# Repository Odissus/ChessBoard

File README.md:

# About

An interactive chess board hardware design based on Arduino Nano ESP32 and KiCad.

| Top | Bottom |
| :---: | :---: |
|  |  |

> [!TIP]
> If you're just interested in manufacturing your own board, see the quick-start section below

It includes:

* Main schematic and PCB project files
* Local symbol, footprint, and 3D model libraries under `lib/`
* Manufacturing export artifacts under `jlcpcbProduction/`
* Utility scripts under `scripts/` for project-related automation

The goal is to keep everything needed to inspect, edit, and manufacture the board inside this repository.

This PCB is based on [Concept Bytes design](https://concept-bytes.com/products/openchess-pcb), along with their [GitHub repository](https://github.com/Concept-Bytes/Open-Chess). The design is new, although heavily insipired by their work and their guides should work in getting you set up on the embedded development side.

This design is optimised for [JLCPCB](https://jlcpcb.com/) production.

# Quick start

1. Head over to releases, and grab the `JLCPCB_Gerber.zip`, `JLCPCB_Bill_of_materials.csv` and `JLCPCB_Positions.csv` files from the latest release.
1. Heaver over to [JLCPCB](https://jlcpcb.com/) to get and instant PCB quote.
1. Upload the `JLCPCB_Gerber.zip`, let JLC process it.
1. Select your desired `PCB colour` (in PCB Specifications) - they're all free
1. Under High-spec Options, select `Mark on PCB` to `2D barcode Only`.
    1. For `Prefix`, choose a sensible name like `ChessBoard`
    1. For `2D Barcode Size` you must select `10*10mm`
    1. For `2D Barcode Position` select `Specify Position`
1. Select PCB Asembly - there is a choice here
    1. Default - economic. You'll have to source the `74HC595N` shift register yourself from a supplier like Mouser, DigiKey, Farnel or Amazon. Ensure you're buing a DIP-16. This should be relatively easy to solder and will reduce the costs by around 40%.
        1. For `PCBA Type`, select `Economic`
        1. For `Assembly Side`, select `Top Side`
        1. Unless you need 5 assembled boards, reduce `PCBA Qty` to `2`
        1. For `Tooling holes` select `Added by Customer`
    1. Standard. JLC will put the shift register in for you. I have not included edge rails or fiducials in the design.
        1. For `PCBA Type`, select `Standard`
        1. For `Assembly Side`, select `Both Sides`
        1. Unless you need 5 assembled boards, reduce `PCBA Qty` to `2`
        1. For `Edge Rails/Fiducials` select `Added by JLCPCB`. Their engineer will modify the design slightly to include the extra rails.
        1. In the `PCB Remark` section above, add in a note that you'd like to have V-cuts to create snappable edge rails.
1. Review your PCB, and click next
1. Upload `JLCPCB_Bill_of_materials.csv` as your BOM file and `JLCPCB_Positions.csv` as your CPL file. Let JLC process the files.
1. You should get the following different parts (assuming you're making 2 boards):
    - (2 * 64 = ) 128 LEDs 
    - (2 * 8 = ) 16 Resistors
    - (2 * 64 = ) 128 Hall effect sensors 
    - (2 * 1 = ) 2 Shift registers (this will only appear if you pick assembly on both sides)
1. Verify component placement i.e. does any part look out of place. If all is well, select next to get your final manufacture quote.
1. Profit?

## Setup

1. Install KiCad (recent stable version recommended).
2. Clone this repository.
3. Open `ChessBoard.kicad_pro` in KiCad.
4. Verify the project libraries resolve correctly (symbols, footprints, and 3D models under `lib/`).

Optional (for helper scripts):

1. Install Python 3.10+.
2. Create and activate a virtual environment.
3. Install script dependencies:

```bash
pip install -r scripts/requirements.txt
```

## Usage

Typical workflow:

1. Open the project in KiCad.
2. Edit schematics in `ChessBoard.kicad_sch` (and related sheets).
3. Update and route the PCB in `ChessBoard.kicad_pcb`.
4. Run DRC/ERC checks before export.
5. Generate manufacturing outputs and keep `jlcpcbProduction/` in sync when changes affect fabrication.

Optional helper scripts can be run from the repository root, for example:

```bash
python scripts/fix3D.py
python scripts/fixColours.py
python scripts/qr_detector.py
```

Review any generated or modified files before committing changes.

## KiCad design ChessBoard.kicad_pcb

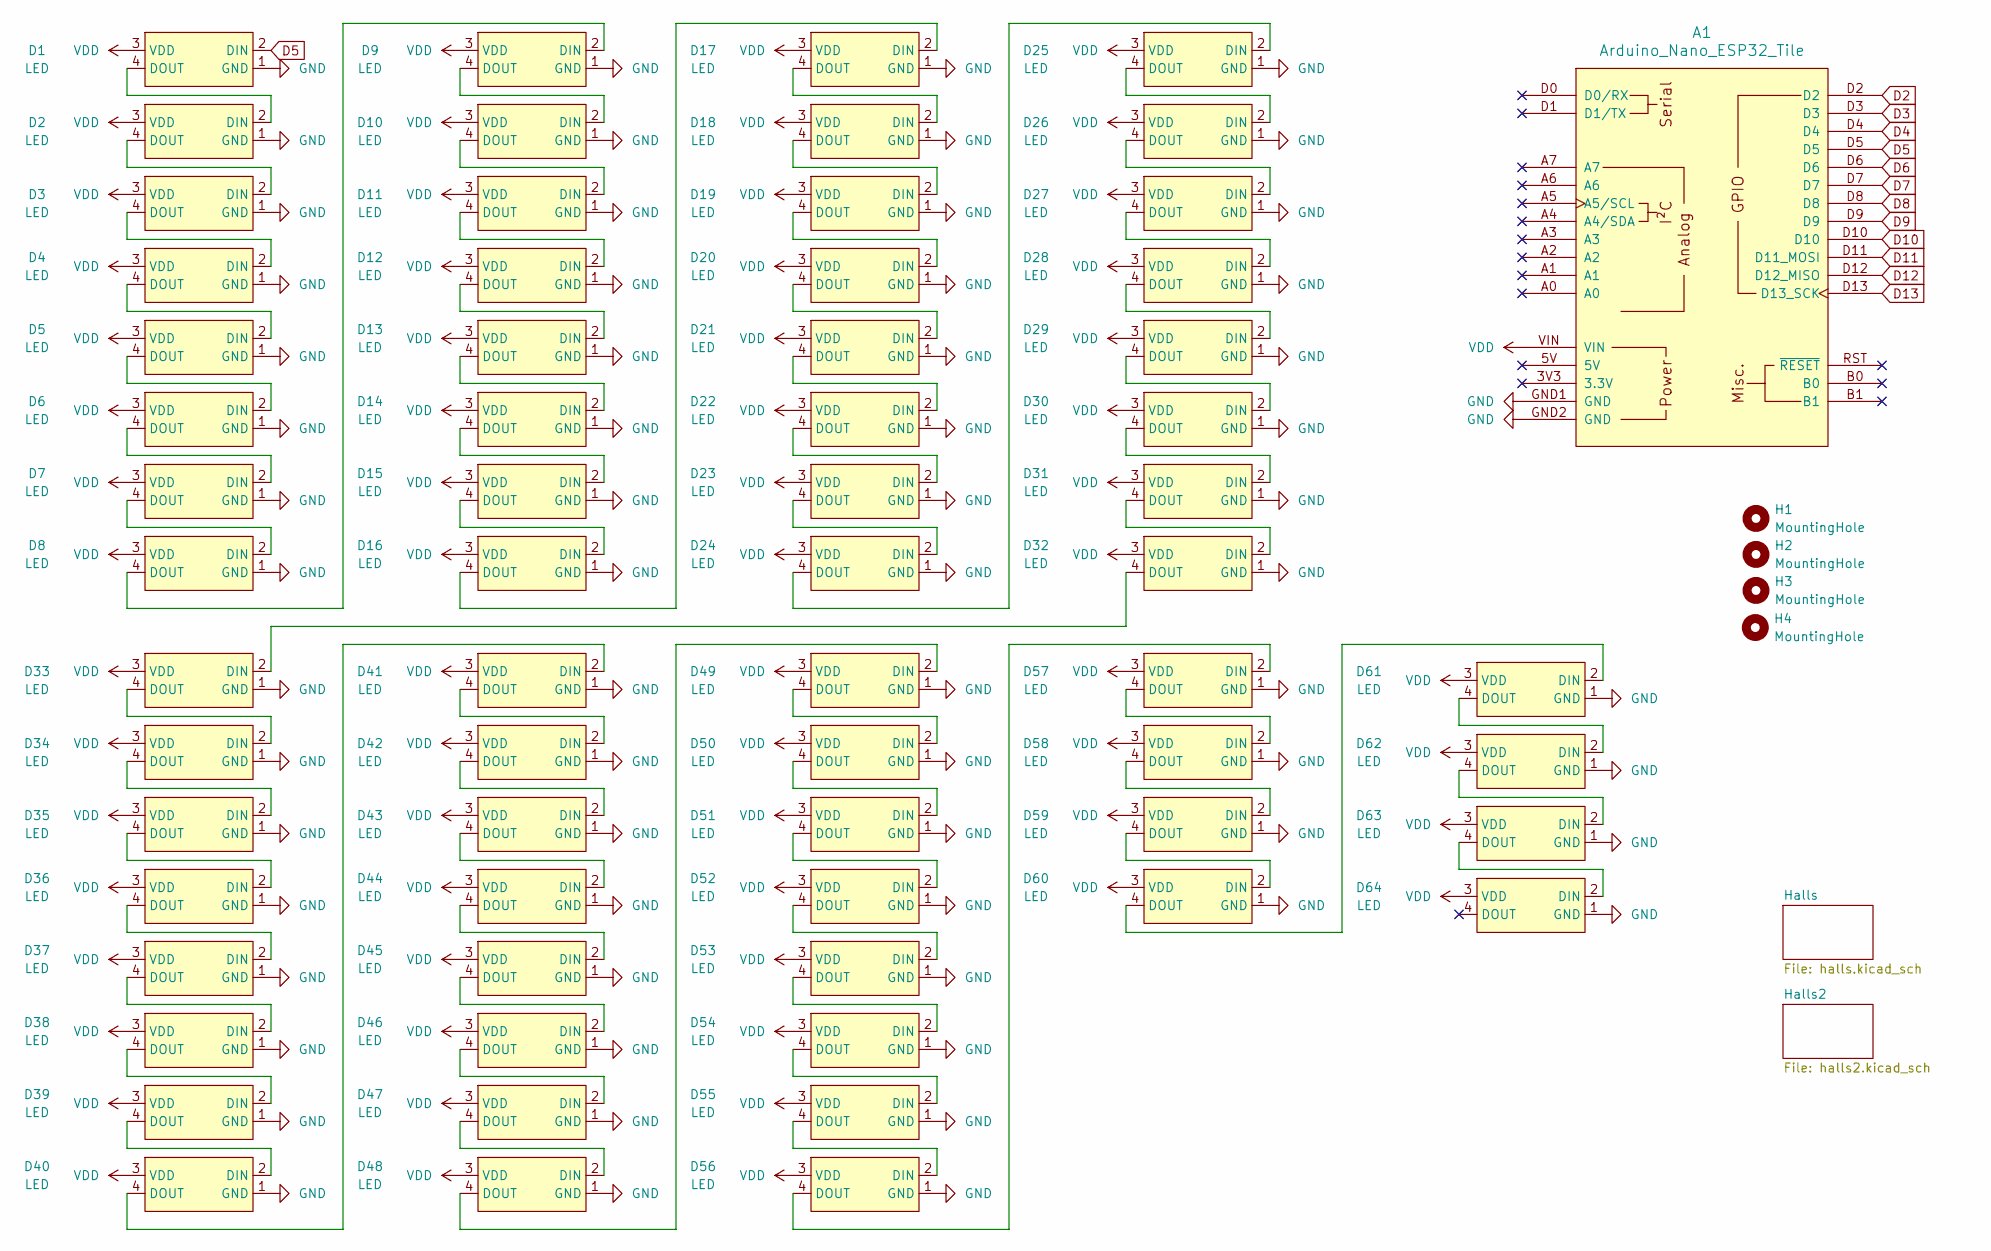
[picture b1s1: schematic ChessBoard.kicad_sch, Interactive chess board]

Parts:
A1: Arduino_Nano_ESP32_Tile
D1, D2, D3, D4, D5, D6, D7, D8, D9, D10, D11, D12, D13, D14, D15, D16, D17, D18, D19, D20, D21, D22, D23, D24, D25, D26, D27, D28, D29, D30, D31, D32, D33, D34, D35, D36, D37, D38, D39, D40, D41, D42, D43, D44, D45, D46, D47, D48, D49, D50, D51, D52, D53, D54, D55, D56, D57, D58, D59, D60, D61, D62, D63, D64: LED; LED-SMD_4P-L5.0-W5.0-TL-2; MPN SKC6812RGBW-BW-B; LCSC Part C5380878
H1, H2, H3, H4: MountingHole; MountingHole_2.1mm

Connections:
D2: A1.D2; also elsewhere on the board
D3: A1.D3; also elsewhere on the board
D4: A1.D4; also elsewhere on the board
D5: A1.D5, D1.2 (DIN)
D6: A1.D6; also elsewhere on the board
D7: A1.D7; also elsewhere on the board
D8: A1.D8; also elsewhere on the board
D9: A1.D9; also elsewhere on the board
D10: A1.D10; also elsewhere on the board
D11: A1.D11 (D11_MOSI); also elsewhere on the board
D12: A1.D12 (D12_MISO); also elsewhere on the board
D13: A1.D13 (D13_SCK); also elsewhere on the board
GND: A1.GND1 (GND), A1.GND2 (GND), D1.1 (GND), D2.1 (GND), D3.1 (GND), D4.1 (GND), D5.1 (GND), D6.1 (GND), D7.1 (GND), D8.1 (GND), D9.1 (GND), D10.1 (GND), D11.1 (GND), D12.1 (GND), D13.1 (GND), D14.1 (GND), D15.1 (GND), D16.1 (GND), D17.1 (GND), D18.1 (GND), D19.1 (GND), D20.1 (GND), D21.1 (GND), D22.1 (GND), D23.1 (GND), D24.1 (GND), D25.1 (GND), D26.1 (GND), D27.1 (GND), D28.1 (GND), D29.1 (GND), D30.1 (GND), D31.1 (GND), D32.1 (GND), D33.1 (GND), D34.1 (GND), D35.1 (GND), D36.1 (GND), D37.1 (GND), D38.1 (GND), D39.1 (GND), D40.1 (GND), D41.1 (GND), D42.1 (GND), D43.1 (GND), D44.1 (GND), D45.1 (GND), D46.1 (GND), D47.1 (GND), D48.1 (GND), D49.1 (GND), D50.1 (GND), D51.1 (GND), D52.1 (GND), D53.1 (GND), D54.1 (GND), D55.1 (GND), D56.1 (GND), D57.1 (GND), D58.1 (GND), D59.1 (GND), D60.1 (GND), D61.1 (GND), D62.1 (GND), D63.1 (GND), D64.1 (GND); also elsewhere on the board
unnamed: D1.4 (DOUT), D2.2 (DIN)
unnamed: D2.4 (DOUT), D3.2 (DIN)
unnamed: D3.4 (DOUT), D4.2 (DIN)
unnamed: D4.4 (DOUT), D5.2 (DIN)
unnamed: D5.4 (DOUT), D6.2 (DIN)
unnamed: D6.4 (DOUT), D7.2 (DIN)
unnamed: D7.4 (DOUT), D8.2 (DIN)
unnamed: D8.4 (DOUT), D9.2 (DIN)
unnamed: D9.4 (DOUT), D10.2 (DIN)
unnamed: D10.4 (DOUT), D11.2 (DIN)
unnamed: D11.4 (DOUT), D12.2 (DIN)
unnamed: D12.4 (DOUT), D13.2 (DIN)
unnamed: D13.4 (DOUT), D14.2 (DIN)
unnamed: D14.4 (DOUT), D15.2 (DIN)
unnamed: D15.4 (DOUT), D16.2 (DIN)
unnamed: D16.4 (DOUT), D17.2 (DIN)
unnamed: D17.4 (DOUT), D18.2 (DIN)
unnamed: D18.4 (DOUT), D19.2 (DIN)
unnamed: D19.4 (DOUT), D20.2 (DIN)
unnamed: D20.4 (DOUT), D21.2 (DIN)
unnamed: D21.4 (DOUT), D22.2 (DIN)
unnamed: D22.4 (DOUT), D23.2 (DIN)
unnamed: D23.4 (DOUT), D24.2 (DIN)
unnamed: D24.4 (DOUT), D25.2 (DIN)
unnamed: D25.4 (DOUT), D26.2 (DIN)
unnamed: D26.4 (DOUT), D27.2 (DIN)
unnamed: D27.4 (DOUT), D28.2 (DIN)
unnamed: D28.4 (DOUT), D29.2 (DIN)
unnamed: D29.4 (DOUT), D30.2 (DIN)
unnamed: D30.4 (DOUT), D31.2 (DIN)
unnamed: D31.4 (DOUT), D32.2 (DIN)
unnamed: D32.4 (DOUT), D33.2 (DIN)
unnamed: D33.4 (DOUT), D34.2 (DIN)
unnamed: D34.4 (DOUT), D35.2 (DIN)
unnamed: D35.4 (DOUT), D36.2 (DIN)
unnamed: D36.4 (DOUT), D37.2 (DIN)
unnamed: D37.4 (DOUT), D38.2 (DIN)
unnamed: D38.4 (DOUT), D39.2 (DIN)
unnamed: D39.4 (DOUT), D40.2 (DIN)
unnamed: D40.4 (DOUT), D41.2 (DIN)
unnamed: D41.4 (DOUT), D42.2 (DIN)
unnamed: D42.4 (DOUT), D43.2 (DIN)
unnamed: D43.4 (DOUT), D44.2 (DIN)
unnamed: D44.4 (DOUT), D45.2 (DIN)
unnamed: D45.4 (DOUT), D46.2 (DIN)
unnamed: D46.4 (DOUT), D47.2 (DIN)
unnamed: D47.4 (DOUT), D48.2 (DIN)
unnamed: D48.4 (DOUT), D49.2 (DIN)
unnamed: D49.4 (DOUT), D50.2 (DIN)
unnamed: D50.4 (DOUT), D51.2 (DIN)
unnamed: D51.4 (DOUT), D52.2 (DIN)
unnamed: D52.4 (DOUT), D53.2 (DIN)
unnamed: D53.4 (DOUT), D54.2 (DIN)
unnamed: D54.4 (DOUT), D55.2 (DIN)
unnamed: D55.4 (DOUT), D56.2 (DIN)
unnamed: D56.4 (DOUT), D57.2 (DIN)
unnamed: D57.4 (DOUT), D58.2 (DIN)
unnamed: D58.4 (DOUT), D59.2 (DIN)
unnamed: D59.4 (DOUT), D60.2 (DIN)
unnamed: D60.4 (DOUT), D61.2 (DIN)
unnamed: D61.4 (DOUT), D62.2 (DIN)
unnamed: D62.4 (DOUT), D63.2 (DIN)
unnamed: D63.4 (DOUT), D64.2 (DIN)
VDD: A1.VIN, D1.3 (VDD), D2.3 (VDD), D3.3 (VDD), D4.3 (VDD), D5.3 (VDD), D6.3 (VDD), D7.3 (VDD), D8.3 (VDD), D9.3 (VDD), D10.3 (VDD), D11.3 (VDD), D12.3 (VDD), D13.3 (VDD), D14.3 (VDD), D15.3 (VDD), D16.3 (VDD), D17.3 (VDD), D18.3 (VDD), D19.3 (VDD), D20.3 (VDD), D21.3 (VDD), D22.3 (VDD), D23.3 (VDD), D24.3 (VDD), D25.3 (VDD), D26.3 (VDD), D27.3 (VDD), D28.3 (VDD), D29.3 (VDD), D30.3 (VDD), D31.3 (VDD), D32.3 (VDD), D33.3 (VDD), D34.3 (VDD), D35.3 (VDD), D36.3 (VDD), D37.3 (VDD), D38.3 (VDD), D39.3 (VDD), D40.3 (VDD), D41.3 (VDD), D42.3 (VDD), D43.3 (VDD), D44.3 (VDD), D45.3 (VDD), D46.3 (VDD), D47.3 (VDD), D48.3 (VDD), D49.3 (VDD), D50.3 (VDD), D51.3 (VDD), D52.3 (VDD), D53.3 (VDD), D54.3 (VDD), D55.3 (VDD), D56.3 (VDD), D57.3 (VDD), D58.3 (VDD), D59.3 (VDD), D60.3 (VDD), D61.3 (VDD), D62.3 (VDD), D63.3 (VDD), D64.3 (VDD); also elsewhere on the board

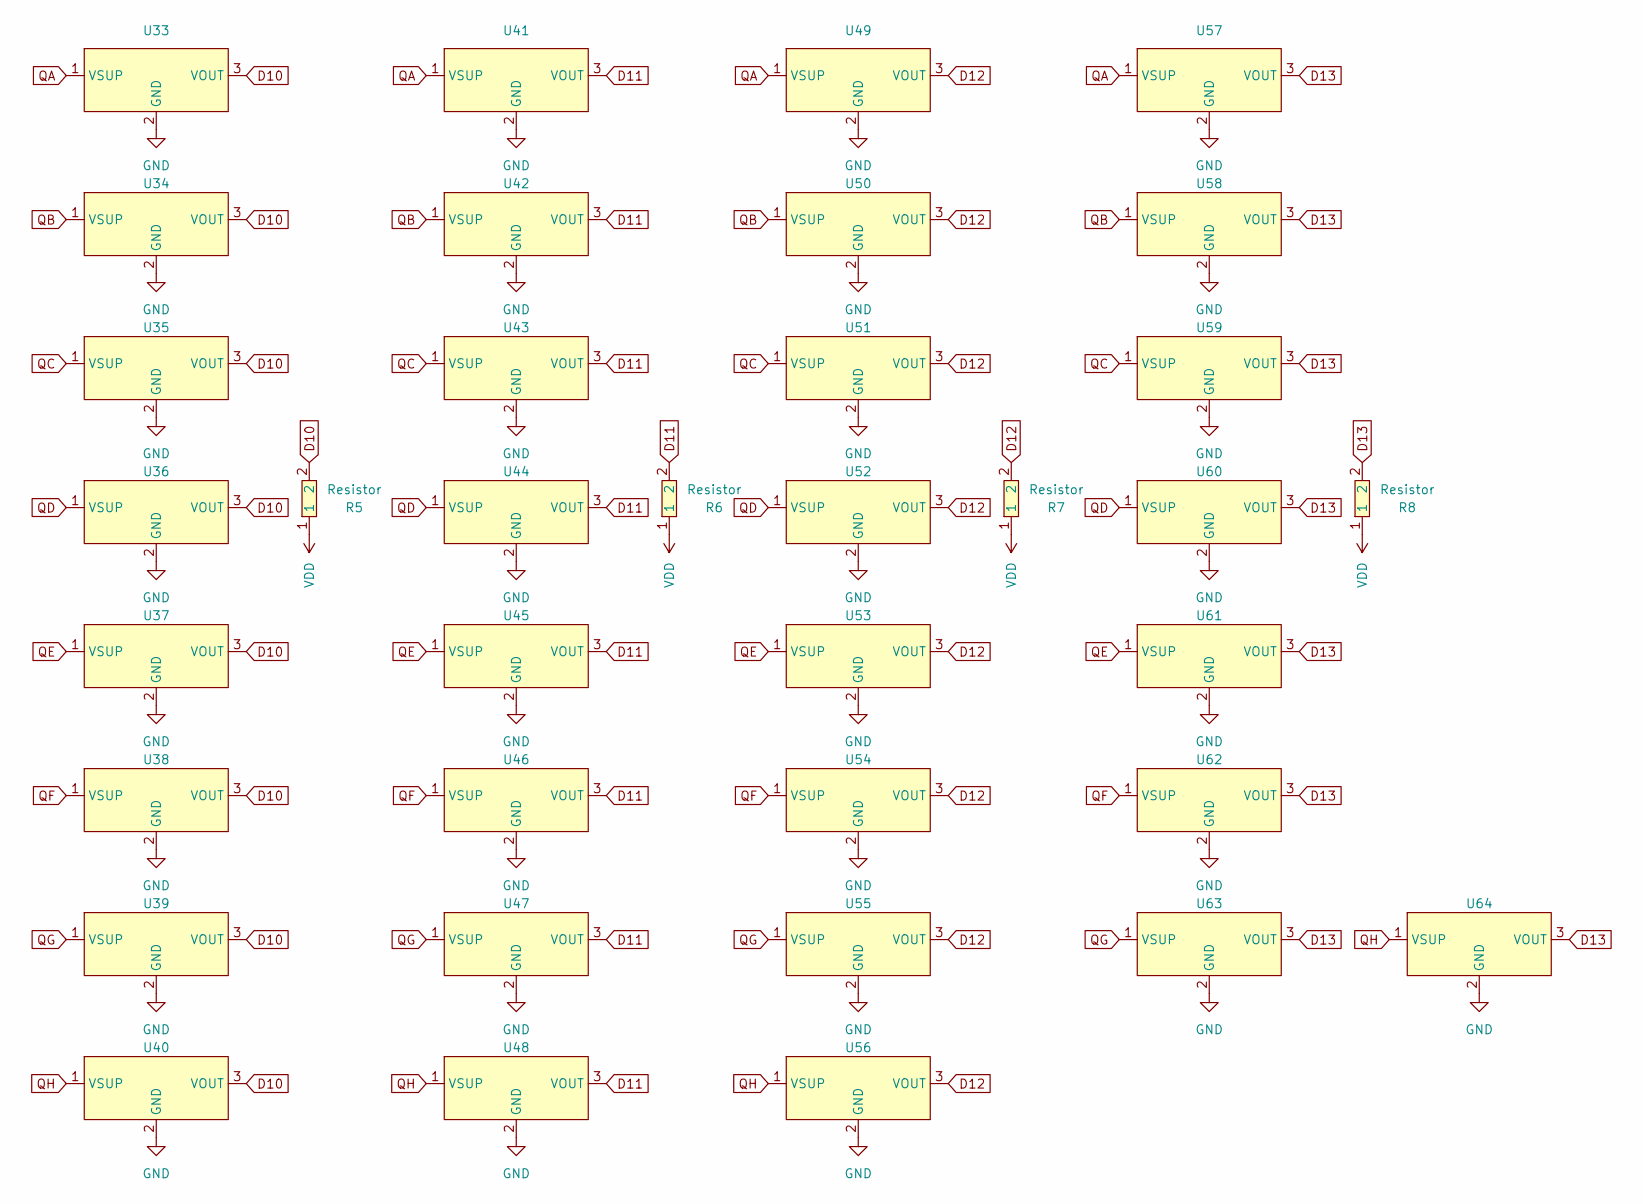
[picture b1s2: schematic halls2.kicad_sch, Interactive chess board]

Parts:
R5, R6, R7, R8: Resistor; R0805; MPN 0805W8F1002T5E; LCSC Part C17414
U33, U34, U35, U36, U37, U38, U39, U40, U41, U42, U43, U44, U45, U46, U47, U48, U49, U50, U51, U52, U53, U54, U55, U56, U57, U58, U59, U60, U61, U62, U63, U64: Hall; SOT-23-3_L2.9-W1.6-P1.90-LS2.8-BR-CW; MPN A3144E-JSM; LCSC Part C18221462

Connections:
D10: R5.2, U33.3 (VOUT), U34.3 (VOUT), U35.3 (VOUT), U36.3 (VOUT), U37.3 (VOUT), U38.3 (VOUT), U39.3 (VOUT), U40.3 (VOUT); also elsewhere on the board
D11: R6.2, U41.3 (VOUT), U42.3 (VOUT), U43.3 (VOUT), U44.3 (VOUT), U45.3 (VOUT), U46.3 (VOUT), U47.3 (VOUT), U48.3 (VOUT); also elsewhere on the board
D12: R7.2, U49.3 (VOUT), U50.3 (VOUT), U51.3 (VOUT), U52.3 (VOUT), U53.3 (VOUT), U54.3 (VOUT), U55.3 (VOUT), U56.3 (VOUT); also elsewhere on the board
D13: R8.2, U57.3 (VOUT), U58.3 (VOUT), U59.3 (VOUT), U60.3 (VOUT), U61.3 (VOUT), U62.3 (VOUT), U63.3 (VOUT), U64.3 (VOUT); also elsewhere on the board
GND: U33.2 (GND), U34.2 (GND), U35.2 (GND), U36.2 (GND), U37.2 (GND), U38.2 (GND), U39.2 (GND), U40.2 (GND), U41.2 (GND), U42.2 (GND), U43.2 (GND), U44.2 (GND), U45.2 (GND), U46.2 (GND), U47.2 (GND), U48.2 (GND), U49.2 (GND), U50.2 (GND), U51.2 (GND), U52.2 (GND), U53.2 (GND), U54.2 (GND), U55.2 (GND), U56.2 (GND), U57.2 (GND), U58.2 (GND), U59.2 (GND), U60.2 (GND), U61.2 (GND), U62.2 (GND), U63.2 (GND), U64.2 (GND); also elsewhere on the board
QA: U33.1 (VSUP), U41.1 (VSUP), U49.1 (VSUP), U57.1 (VSUP); also elsewhere on the board
QB: U34.1 (VSUP), U42.1 (VSUP), U50.1 (VSUP), U58.1 (VSUP); also elsewhere on the board
QC: U35.1 (VSUP), U43.1 (VSUP), U51.1 (VSUP), U59.1 (VSUP); also elsewhere on the board
QD: U36.1 (VSUP), U44.1 (VSUP), U52.1 (VSUP), U60.1 (VSUP); also elsewhere on the board
QE: U37.1 (VSUP), U45.1 (VSUP), U53.1 (VSUP), U61.1 (VSUP); also elsewhere on the board
QF: U38.1 (VSUP), U46.1 (VSUP), U54.1 (VSUP), U62.1 (VSUP); also elsewhere on the board
QG: U39.1 (VSUP), U47.1 (VSUP), U55.1 (VSUP), U63.1 (VSUP); also elsewhere on the board
QH: U40.1 (VSUP), U48.1 (VSUP), U56.1 (VSUP), U64.1 (VSUP); also elsewhere on the board
VDD: R5.1, R6.1, R7.1, R8.1; also elsewhere on the board

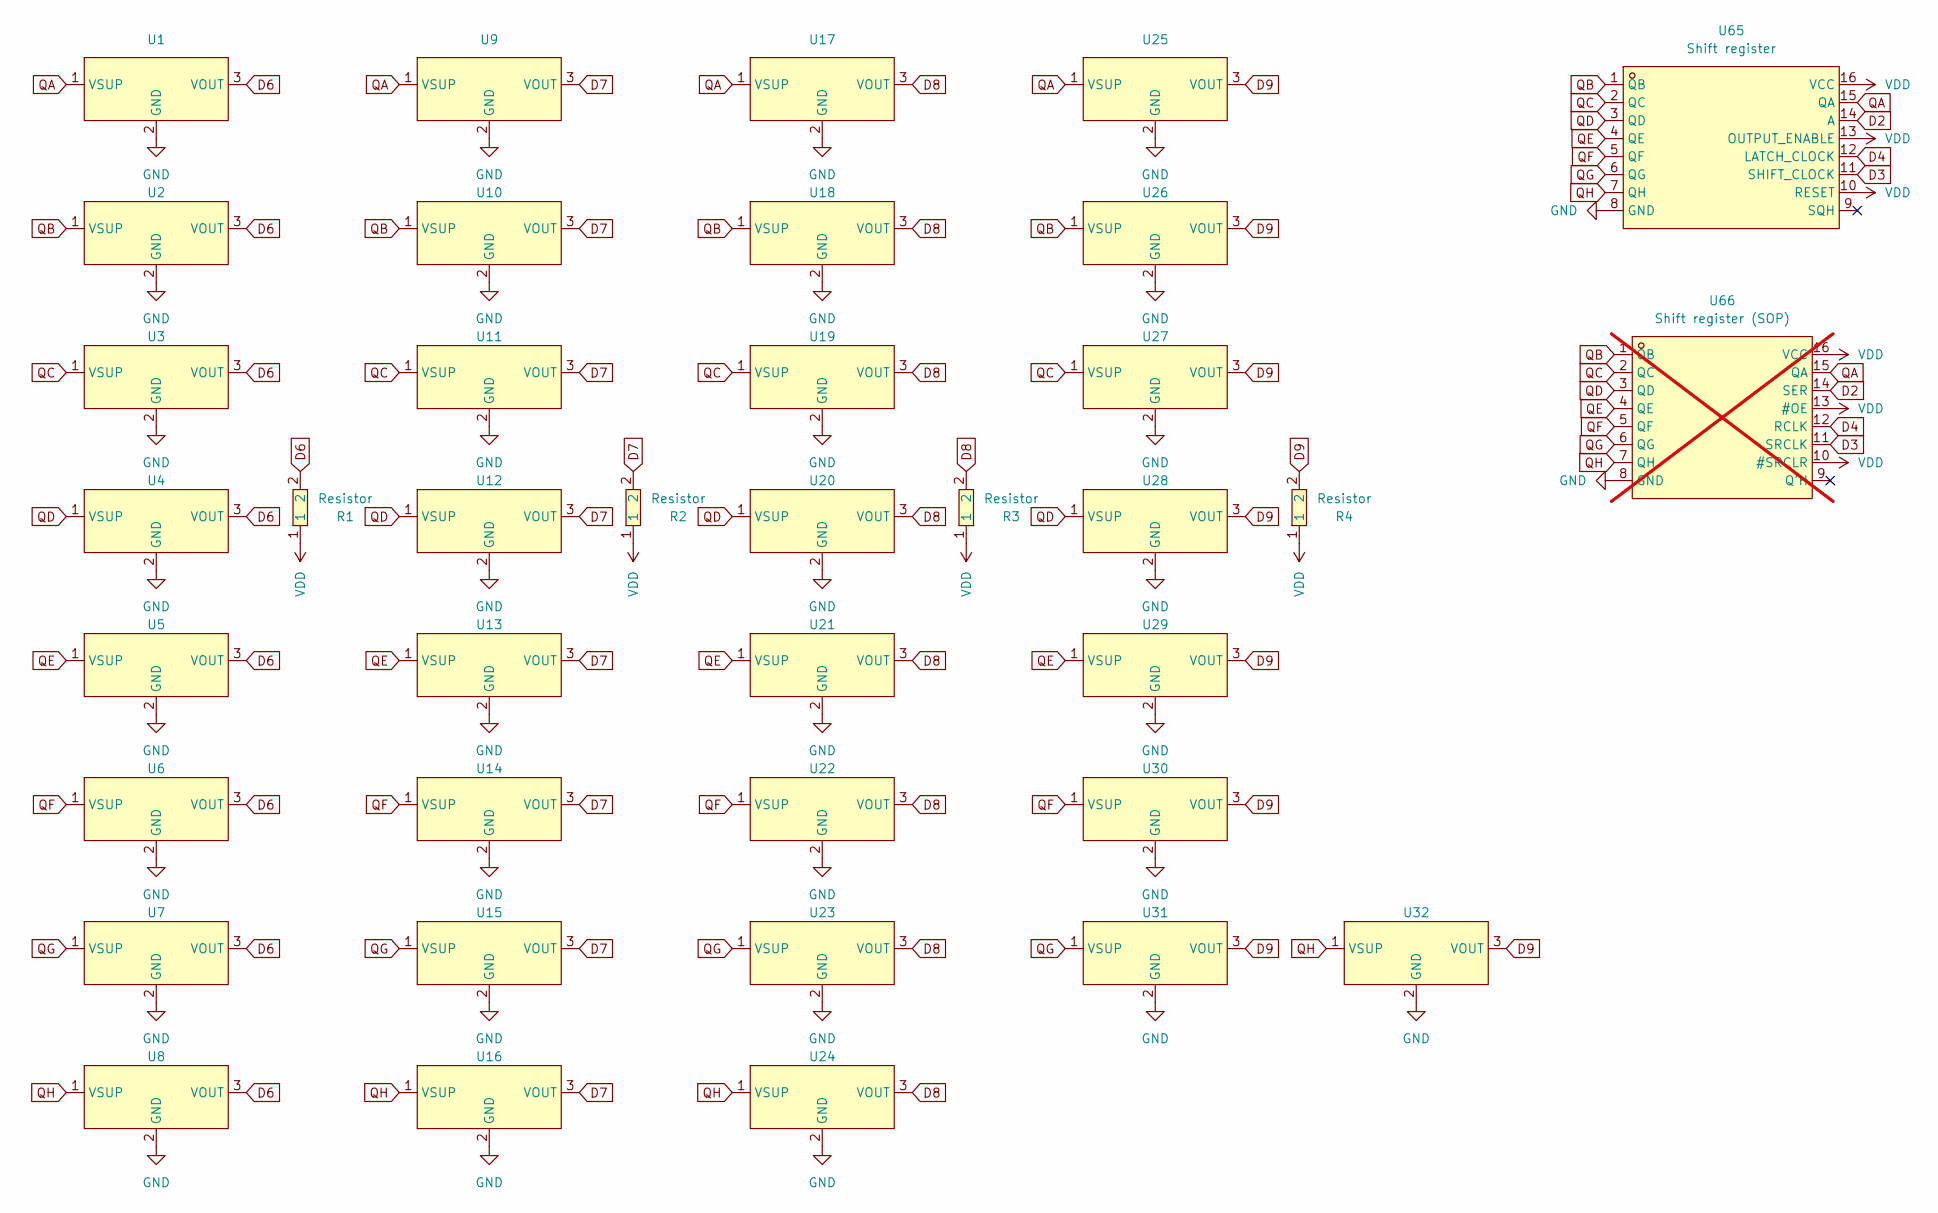
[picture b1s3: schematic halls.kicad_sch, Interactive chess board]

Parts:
R1, R2, R3, R4: Resistor; R0805; MPN 0805W8F1002T5E; LCSC Part C17414
U1, U2, U3, U4, U5, U6, U7, U8, U9, U10, U11, U12, U13, U14, U15, U16, U17, U18, U19, U20, U21, U22, U23, U24, U25, U26, U27, U28, U29, U30, U31, U32: Hall; SOT-23-3_L2.9-W1.6-P1.90-LS2.8-BR-CW; MPN A3144E-JSM; LCSC Part C18221462
U65: Shift register; DIP-16_L20.0-W6.4-P2.54-LS7.6-BL; MPN 74HC595N; LCSC Part C507175
U66: Shift register (SOP); SOP-16_L10.3-W5.4-P1.27-LS7.8-BL; MPN SN74HC595NSR; LCSC Part C191873; not fitted

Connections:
D2: U65.14 (A), U66.14 (SER); also elsewhere on the board
D3: U65.11 (SHIFT_CLOCK), U66.11 (SRCLK); also elsewhere on the board
D4: U65.12 (LATCH_CLOCK), U66.12 (RCLK); also elsewhere on the board
D6: R1.2, U1.3 (VOUT), U2.3 (VOUT), U3.3 (VOUT), U4.3 (VOUT), U5.3 (VOUT), U6.3 (VOUT), U7.3 (VOUT), U8.3 (VOUT); also elsewhere on the board
D7: R2.2, U9.3 (VOUT), U10.3 (VOUT), U11.3 (VOUT), U12.3 (VOUT), U13.3 (VOUT), U14.3 (VOUT), U15.3 (VOUT), U16.3 (VOUT); also elsewhere on the board
D8: R3.2, U17.3 (VOUT), U18.3 (VOUT), U19.3 (VOUT), U20.3 (VOUT), U21.3 (VOUT), U22.3 (VOUT), U23.3 (VOUT), U24.3 (VOUT); also elsewhere on the board
D9: R4.2, U25.3 (VOUT), U26.3 (VOUT), U27.3 (VOUT), U28.3 (VOUT), U29.3 (VOUT), U30.3 (VOUT), U31.3 (VOUT), U32.3 (VOUT); also elsewhere on the board
GND: U1.2 (GND), U2.2 (GND), U3.2 (GND), U4.2 (GND), U5.2 (GND), U6.2 (GND), U7.2 (GND), U8.2 (GND), U9.2 (GND), U10.2 (GND), U11.2 (GND), U12.2 (GND), U13.2 (GND), U14.2 (GND), U15.2 (GND), U16.2 (GND), U17.2 (GND), U18.2 (GND), U19.2 (GND), U20.2 (GND), U21.2 (GND), U22.2 (GND), U23.2 (GND), U24.2 (GND), U25.2 (GND), U26.2 (GND), U27.2 (GND), U28.2 (GND), U29.2 (GND), U30.2 (GND), U31.2 (GND), U32.2 (GND), U65.8 (GND), U66.8 (GND); also elsewhere on the board
QA: U1.1 (VSUP), U9.1 (VSUP), U17.1 (VSUP), U25.1 (VSUP), U65.15 (QA), U66.15 (QA); also elsewhere on the board
QB: U2.1 (VSUP), U10.1 (VSUP), U18.1 (VSUP), U26.1 (VSUP), U65.1 (QB), U66.1 (QB); also elsewhere on the board
QC: U3.1 (VSUP), U11.1 (VSUP), U19.1 (VSUP), U27.1 (VSUP), U65.2 (QC), U66.2 (QC); also elsewhere on the board
QD: U4.1 (VSUP), U12.1 (VSUP), U20.1 (VSUP), U28.1 (VSUP), U65.3 (QD), U66.3 (QD); also elsewhere on the board
QE: U5.1 (VSUP), U13.1 (VSUP), U21.1 (VSUP), U29.1 (VSUP), U65.4 (QE), U66.4 (QE); also elsewhere on the board
QF: U6.1 (VSUP), U14.1 (VSUP), U22.1 (VSUP), U30.1 (VSUP), U65.5 (QF), U66.5 (QF); also elsewhere on the board
QG: U7.1 (VSUP), U15.1 (VSUP), U23.1 (VSUP), U31.1 (VSUP), U65.6 (QG), U66.6 (QG); also elsewhere on the board
QH: U8.1 (VSUP), U16.1 (VSUP), U24.1 (VSUP), U32.1 (VSUP), U65.7 (QH), U66.7 (QH); also elsewhere on the board
VDD: R1.1, R2.1, R3.1, R4.1, U65.10 (RESET), U65.13 (OUTPUT_ENABLE), U65.16 (VCC), U66.10 (#SRCLR), U66.13 (#OE), U66.16 (VCC); also elsewhere on the board

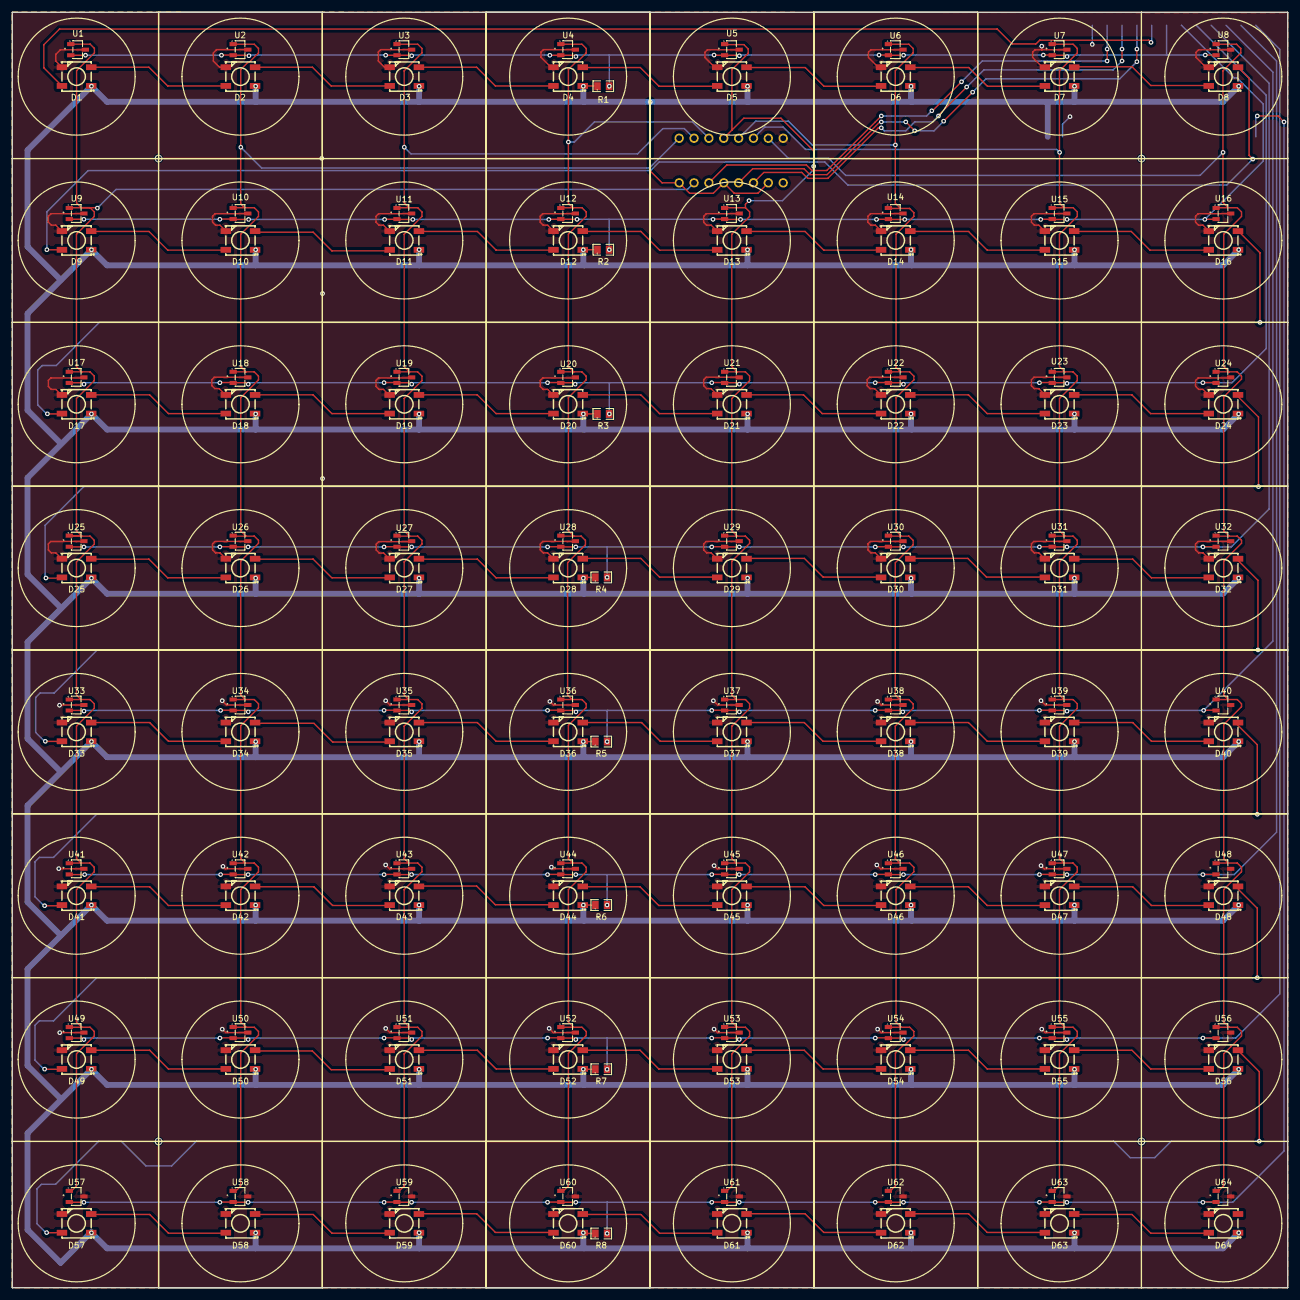
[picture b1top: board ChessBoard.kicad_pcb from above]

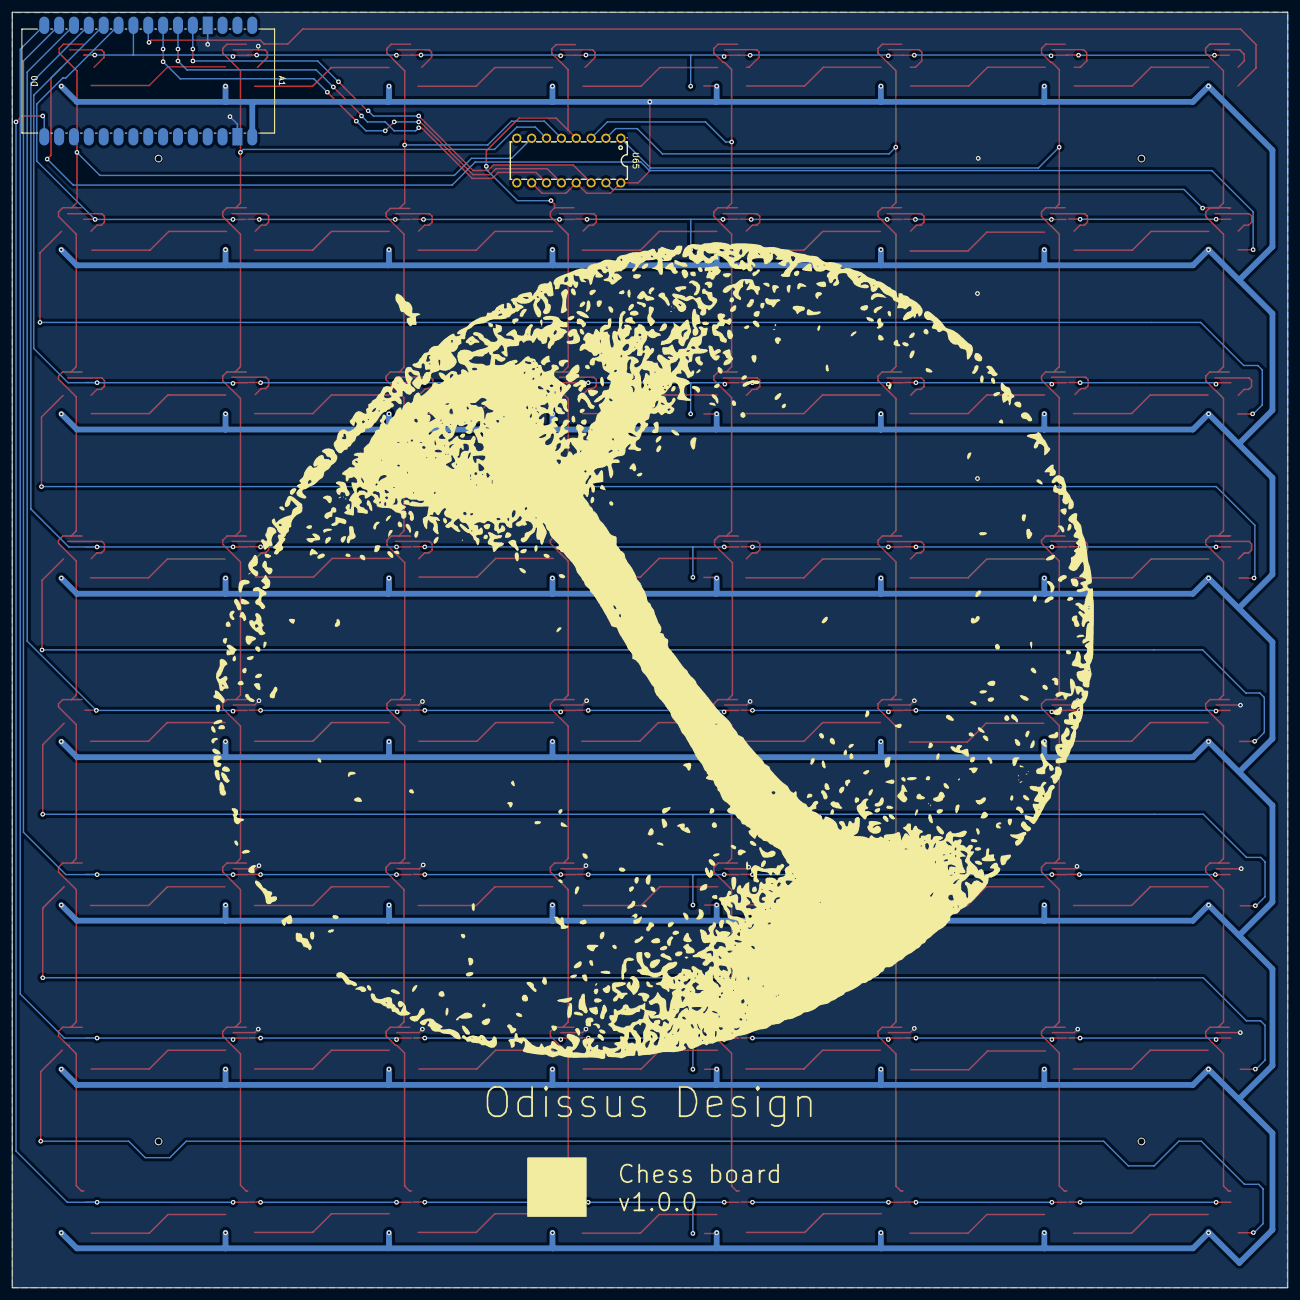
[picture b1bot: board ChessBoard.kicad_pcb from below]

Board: 2 copper layers, 218.0 x 218.0 mm, 142 parts (2 on the bottom side), 85 nets.

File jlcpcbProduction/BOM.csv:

Comment,Designator,Footprint,LCSC,Quantity
Hall,"U1,U10,U11,U12,U13,U14,U15,U16,U17,U18,U19,U2,U20,U21,U22,U23,U24,U25,U26,U27,U28,U29,U3,U30,U31,U32,U33,U34,U35,U36,U37,U38,U39,U4,U40,U41,U42,U43,U44,U45,U46,U47,U48,U49,U5,U50,U51,U52,U53,U54,U55,U56,U57,U58,U59,U6,U60,U61,U62,U63,U64,U7,U8,U9",SOT-23-3_L2.9-W1.6-P1.90-LS2.8-BR-CW,C18221462,64
LED,"D1,D10,D11,D12,D13,D14,D15,D16,D17,D18,D19,D2,D20,D21,D22,D23,D24,D25,D26,D27,D28,D29,D3,D30,D31,D32,D33,D34,D35,D36,D37,D38,D39,D4,D40,D41,D42,D43,D44,D45,D46,D47,D48,D49,D5,D50,D51,D52,D53,D54,D55,D56,D57,D58,D59,D6,D60,D61,D62,D63,D64,D7,D8,D9",LED-SMD_4P-L5.0-W5.0-TL-2,C5380878,64
Resistor,"R1,R2,R3,R4,R5,R6,R7,R8",R0805,C17414,8
Shift register,U65,DIP-16_L20.0-W6.4-P2.54-LS7.6-BL,C507175,1
